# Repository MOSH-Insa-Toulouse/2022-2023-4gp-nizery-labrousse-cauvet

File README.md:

# *PROJET CAPTEUR - CG-4127-GAF*

## Introduction : Description du projet, Cahier des charges et Livrables 

Ce projet s’inscrit dans l’UF “Du capteur au banc de test” de 4ème année de Génie Physique de l’INSA Toulouse. Il s’inscrit dans une démarche low-tech de développement d’un capteur de contrainte et d’un système de mesure permettant la caractérisation du capteur. Il s’appuie sur l’étude de capteurs de contrainte en graphite (système granulaire) dont la résistance varie suivant la déformation du capteur (Pencil Drawn Strain Gauges and Chemiresistors on Paper Cheng-Wei Lin*, Zhibo Zhao*, Jaemyung Kim & Jiaxing Huang Department of Materials Science and Engineering, Northwestern University 2220 Campus Drive, Evanston, IL, 60208, USA).  
Ce travail comprend le design et la fabrication d’un shield Arduino incluant le capteur graphite couplé à un circuit analogique communiquant via un microcontrôleur à une application Android.
Dans un premier temps, nous avons simulé le comportement du circuit analogique sur le logiciel LTSpice. Ce circuit a le double rôle d’amplifier (via un amplificateur transimpédance) et de filtrer le signal délivré par le capteur.  
Ensuite, nous avons réalisé un code Arduino permettant la mesure de résistance et le contrôle des différents éléments du circuit (écran OLED, module Bluetooth et potentiomètre digital). Nous avons préalablement testé notre circuit et le code en montant les différents éléments sur une breadboard, puis nous avons designé un PCB grâce au logiciel KiCad constituant le shield se fixant sur une carte Arduino UNO.  
Après tirage du PCB, nous avons soudé l’ensemble des composants du circuit et développé une application Android sur le site MIT App Inventor affichant les mesures de résistance via transmission Bluetooth.  
Enfin, nous avons réalisé une datasheet caractérisant le capteur pour différents types de crayons graphites en mesurant la variation de résistance relative en fonction de la déformation du capteur grâce à un banc de mesure existant fabriqué en impression 3D.

### Livrables

Les livrables pour ce projet sont :

* Un shield PCB se fixant à une carte Arduino UNO comprenant un amplificateur transimpédance, un module Bluetooth, un écran OLED et un potentiomètre digital.
* Un code Arduino gérant la mesure de résistance du capteur graphite, la communication avec le module Bluetooth, l'affichage à l'écran OLED et la gestion du potentiomètre digital.
* Un Android APK qui gère l'interfaçage du système de mesure sur un téléphone Android.
* La datasheet du capteur de contrainte graphite.

## Matériel nécessaire
* 1 carte Arduino Uno
* 2 Résistance de 100kΩ
* 1 Résistance de 1kΩ
* 1 Potentiomètre digital MCP-41050
* 2 Condensateurs 100nF
* 1 Condensateurs 1µF
* 1 AOP LTC1050
* 1 Écran OLED01
* 1 Module Bluetooth HC-05

## Simulation du circuit transimpédance avec le logiciel LTSpice 

Nous avons réalisé la simulation électrique du circuit associé au shield sur le logiciel LTSpice. Voici le schéma du circuit simulé : 

Le capteur de graphite délivre un courant de 100 nA qui représente un signal trop faible pour que le microcontrôleur de la carte Arduino détecte les variations du signal. L’amplificateur transimpédance permet donc de transformer le signal de courant en tension et de l’amplifier. Le circuit est ensuite constitué de divers filtres permettant d’atténuer le bruit lié à l'environnement de la mesure (50Hz, hautes fréquences…).
Plusieurs tests ont été effectués sur le circuit et sur les filtres pour connaître le rôle de chacun d’eux et vérifier sa compatibilité avec la carte Arduino qui gère l’acquisition des données.

## Code arduino

Le code .ino donne les instructions à l’arduino pour traiter les informations reçues par le capteur graphite et pour envoyer les informations au module bluetooth HC-05 qui communique avec l’application APK, au potentiomètre digital ainsi qu’à l’écran OLED. Différentes bibliothèques sont incluses, la bibliothèque Adafruit_SSD1306 permet de faciliter la communication avec l’écran OLED, la bibliothèque SPI nous permet d’écrire au potentiomètre digital ses nouvelles valeurs au besoin, SoftwareSerial gère la communication avec l’appareil bluetooth HC-05. Le code de l’arduino permet donc plusieurs choses : 
* Calculer la résistance du capteur graphite en temps réel
* Modifier la valeur de la résistance du potentiomètre digital, ce qui nous permet de régler la sensibilité de la mesure, ainsi que de capter des signaux dans l’intervalle de bits [0:1023] dans lequel l’arduino est limité.
* Afficher la résistance du capteur graphite et la résistance du potentiomètre digital sur l’écran OLED
* Communiquer à l’application la valeur en bits du signal du capteur graphite en compressant sa valeur sur un byte, qui pourra être analysé par l’application APK.

## Création du PCB sur Kicad 

Cette partie du projet consistait à concevoir le PCB du circuit transimpédance sur le logiciel Kicad. En partant d’un template d’une carte Arduino Uno, il a fallu : 
* Concevoir la schématique du circuit transimpédance en créant des symboles pour les composants non existants dans la base de donnée du logiciel
* Concevoir les empreintes réelles de ces composants non existants en prenant en compte leurs caractéristiques physiques (nombres de pins, distance entre les pins, géométrie des empreintes…)
* Effectuer le routage du circuit à partir du chevelu implémenté grâce à la vue schématique du circuit
* Poser le plan de masse pour référencer les pistes au GND

Vous trouverez ci-dessous l’intégralité des symboles et empreintes créées ainsi que la vue schématique du circuit et le PCB final.

### Symboles et empreintes 

* Module Bluetooth HC-05

* Amplificateur LTC1050

* Ecran OLED

* Potentiomètre digital MCP41050

### Schéma Complet

### PCB

## Fabrication du Shield
 
### Réalisation PCB

Voici ci-dessus le circuit imprimé réalisé à partir d’un calque de PCB. 

Le PCB a été réalisé au sein de deux départements de l’INSA Toulouse, le Génie Électrique et Informatique et le Génie Physique. Il a été fabriqué avec une plaquette d’époxy recouverte d’une couche de cuivre d’environ 60𝝻m. Nous avons imprimé sur du calque le circuit ci-dessus, puis nous avons insolé aux UVs notre plaquette avec ce calque pendant une dizaine de minutes. Après avoir retiré la partie de résine non isolée avec un révélateur, nous avons plongé notre plaquette dans un bain de percholorure de fer. Cela a permis de retirer le cuivre qui n’était pas protégé et de révéler les pistes de notre circuit.

### Perçage et soudures 

Une fois le PCB réalisé, il faut percer avec une perceuse électrique les trous pour y mettre les différents composants. Nous avons utilisé deux tailles de pointes pour percer les trous:
un de diamètre 0,8mm pour tous les différents composants et headers des modules OLED et Bluetooth
un de diamètre 1mm pour les broches de connexion de la carte Arduino Uno

Nous avons aussi dû percer deux trous pour y insérer un via pour relier deux points de masse (cela était prévu dans le schéma Kicad).

## Application téléphone APK

Nous avons développé une application Android à l’aide du site MIT App Inventor. Cette application permet de recevoir les données de la carte Arduino par connexion Bluetooth avec le module HC-05 implémenté sur le shield de la carte Arduino. Après connexion Bluetooth, un graphe se dessine permettant de suivre la résistance du capteur graphite en fonction du temps et des contraintes qui lui sont appliquées. La valeur de cette résistance est également affichée implicitement en plus de la valeur de la de résistance du potentiomètre digital.

## Banc de test  

Nous utilisons ce banc de test composé de 7 demi cylindres de différents diamètres allant de 2 à 5 cm avec un pax de 0,5 cm. Nous posons le capteur sur chacun des cylindres et appliquons donc une déformation  sur celui-ci. Cette déformation se retrouve avec la formule ci-dessous : 
$$\epsilon = \frac{e}{2r}$$ 
avec e l’épaisseur du capteur et r le rayon de courbure donc le rayon de chaque demi cylindre.
Nous avons réalisé les mesures en compression et en tension pour chacun de nos capteurs.  

### Résultats obtenus

Vous retrouverez les résultats obtenus avec notre banc de test dans la datasheet [ici](Datasheet/Datasheet_CG-4127-GAF.docx).

### Analyse et pistes d’améliorations

Lors de nos mesures, nous devions reprendre le R0 à chaque essai car celui-ci augmentait entre-temps. Le papier trop fragile, s'abîmait et rendait plus difficile la conduction des électrons, la résistance augmente donc. Il serait donc envisageable de prendre un papier plus résistant qui ne se déformerait pas de manière permanente après chaque mesure.

On peut également penser à l'utilisation d'un dispositif à base d'un servomoteur, en remplacement de notre banc de test, car celui-ci nous permettrait de reproduire les expériences de manière plus fiable, avec tout le temps la même tension/compression exercée entre les différents capteurs.

Afin d'avoir une excellente sensibilité pour toutes les plages de résistance, on aurait pu augmenter le nombre de valeurs de résistance du potentiomètre qui se règlent automatiquement.

## Datasheet 

La datasheet de notre capteur est disponible dans le dossier Datasheet [ici](Datasheet/Datasheet_CG-4127-GAF.docx).

## *Auteurs*

Si vous avez des remarques ou questions complémentaires sur ce projet, n’hésitez pas à nous contacter :

Guillaume Cauvet : cauvet@insa-toulouse.fr  
Fabien Labrousse : labrousse@insa-toulouse.fr  
Audrey Nizery : nizery@insa-toulouse.fr

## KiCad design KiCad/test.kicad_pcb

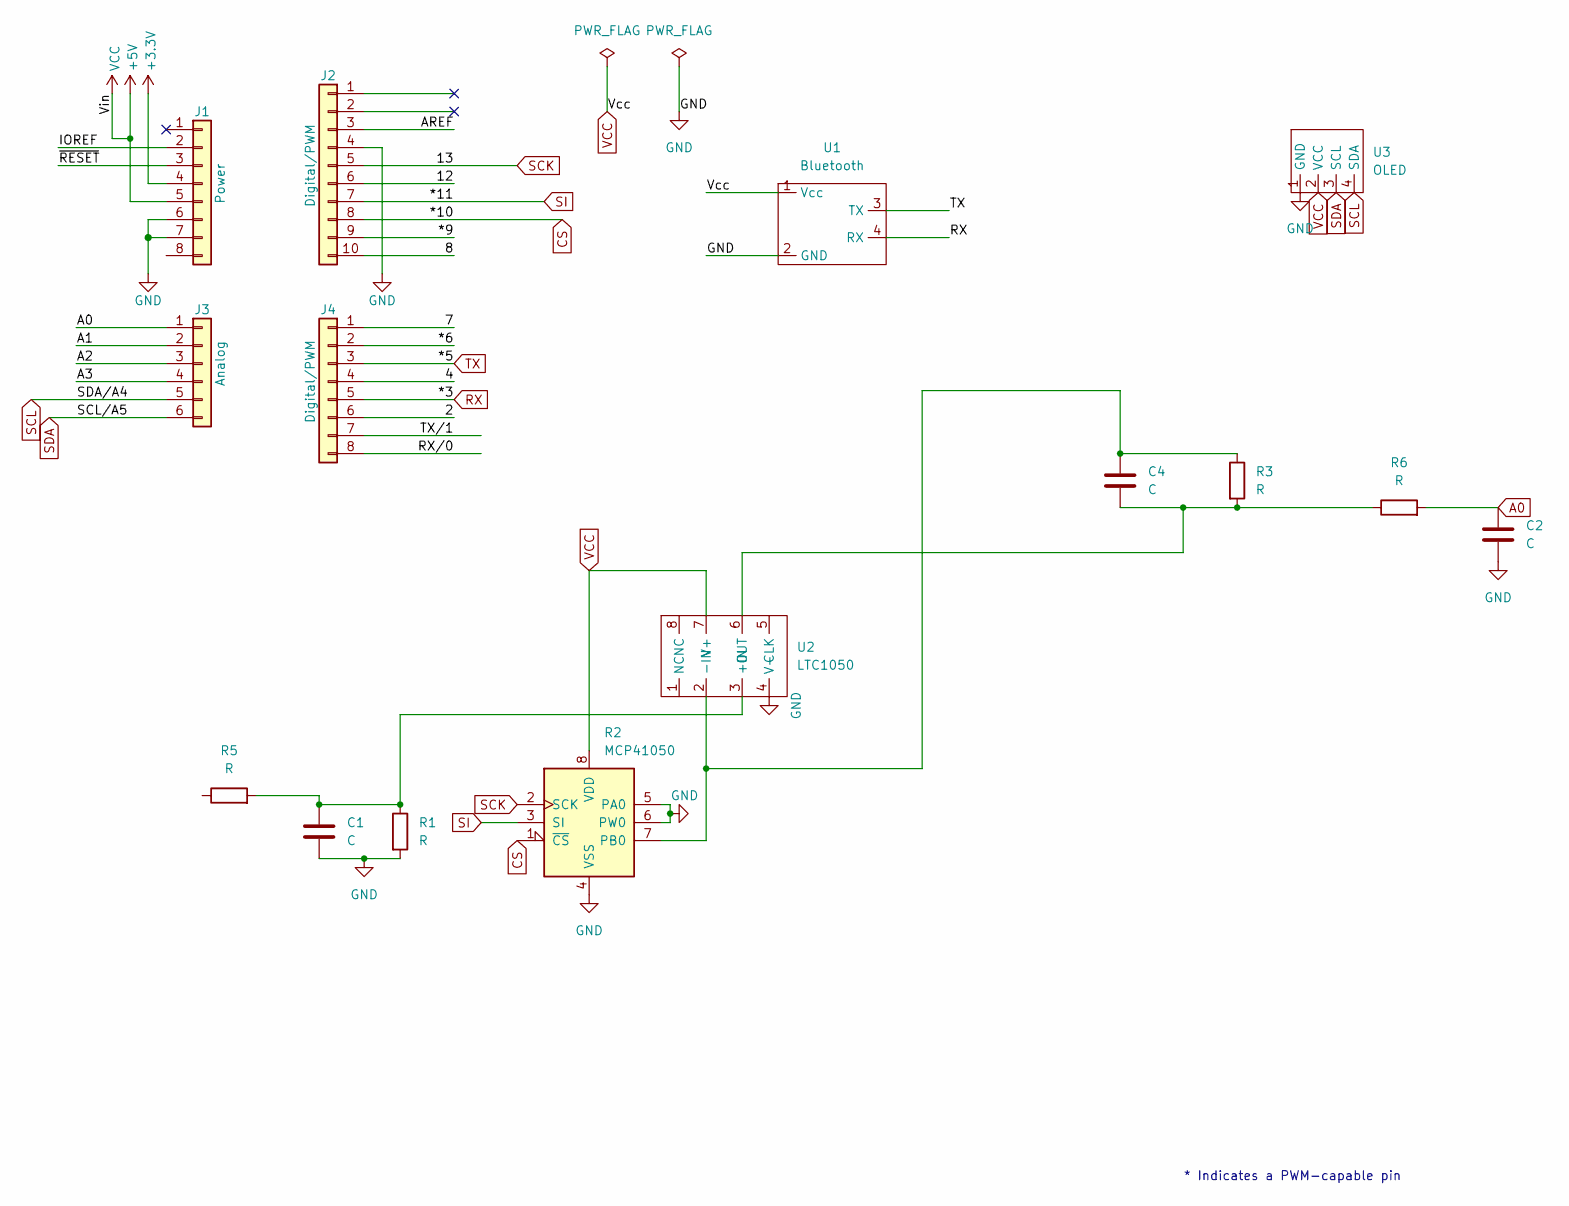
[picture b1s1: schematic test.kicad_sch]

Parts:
C1, C2: C; CP_Radial_Tantal_D5.5mm_P2.50mm
C4: C; C_Rect_L7.0mm_W4.5mm_P5.00mm
J1: Power; PinSocket_1x08_P2.54mm_Vertical
J2: Digital/PWM; PinSocket_1x10_P2.54mm_Vertical
J3: Analog; PinSocket_1x06_P2.54mm_Vertical
J4: Digital/PWM; PinSocket_1x08_P2.54mm_Vertical
R1, R3, R5, R6: R; R_Axial_DIN0204_L3.6mm_D1.6mm_P5.08mm_Horizontal
R2: MCP41050; Pot_Digital
U1: Bluetooth
U2: LTC1050
U3: OLED

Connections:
+3V3: J1.4
/2: J4.6
/4: J4.4
/7: J4.1
/8: J2.10
/12: J2.6
/*6: J4.2
/*9: J2.9
/A1: J3.2
/A2: J3.3
/A3: J3.4
/AREF: J2.3
/IOREF: J1.2
/RX/0: J4.8
/TX/1: J4.7
/~RESET: J1.3
A0: C2.1, J3.1, R6.2
CS: J2.8, R2.1 (~CS)
GND: C1.2, C2.2, J1.6, J1.7, J2.4, R1.2, R2.4 (VSS), R2.5 (PA0), R2.6 (PW0), U1.2 (GND), U2.4 (V-), U3.1 (GND)
unnamed: C1.1, R1.1, R5.2, U2.3 (+IN)
unnamed: C4.1, R2.7 (PB0), R3.1, U2.2 (-IN)
unnamed: C4.2, R3.2, R6.1, U2.6 (OUT)
RX: J4.5, U1.4 (RX)
SCK: J2.5, R2.2 (SCK)
SCL: J3.5, U3.4 (SDA)
SDA: J3.6, U3.3 (SCL)
SI: J2.7, R2.3 (SI)
TX: J4.3, U1.3 (TX)
VCC: J1.5, R2.8 (VDD), U1.1 (Vcc), U2.7 (V+), U3.2 (VCC)

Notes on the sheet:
* Indicates a PWM-capable pin

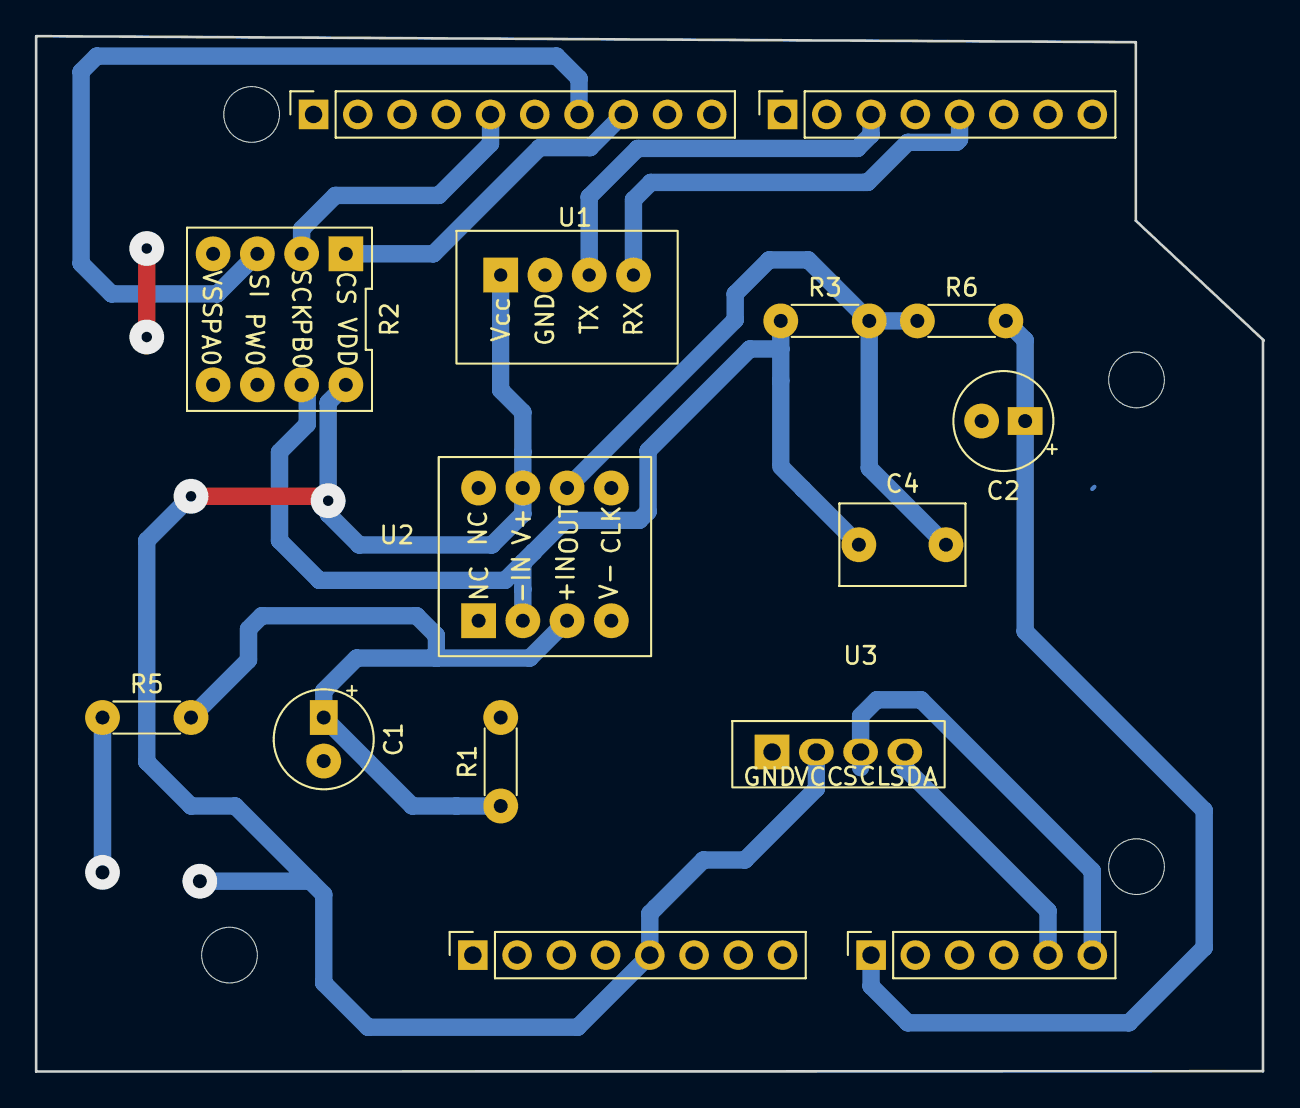
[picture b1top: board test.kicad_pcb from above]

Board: 2 copper layers, 70.5 x 59.4 mm, 19 parts (0 on the bottom side), 13 nets.

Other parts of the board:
MH1, MH2, MH3, MH4: MountingHole_3.2mm

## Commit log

2023-02-01 Ajout to do list
2023-02-01 Ajout TODO list
2023-02-01 Add Checkbox
2023-02-01 decoller to do
2023-02-01 rajout test
2023-05-12 Create Datasheet_CG-4127-GAF
2023-05-12 Create Code
2023-05-12 Create KiCad
2023-05-12 Create APK
2023-05-12 Create Images
